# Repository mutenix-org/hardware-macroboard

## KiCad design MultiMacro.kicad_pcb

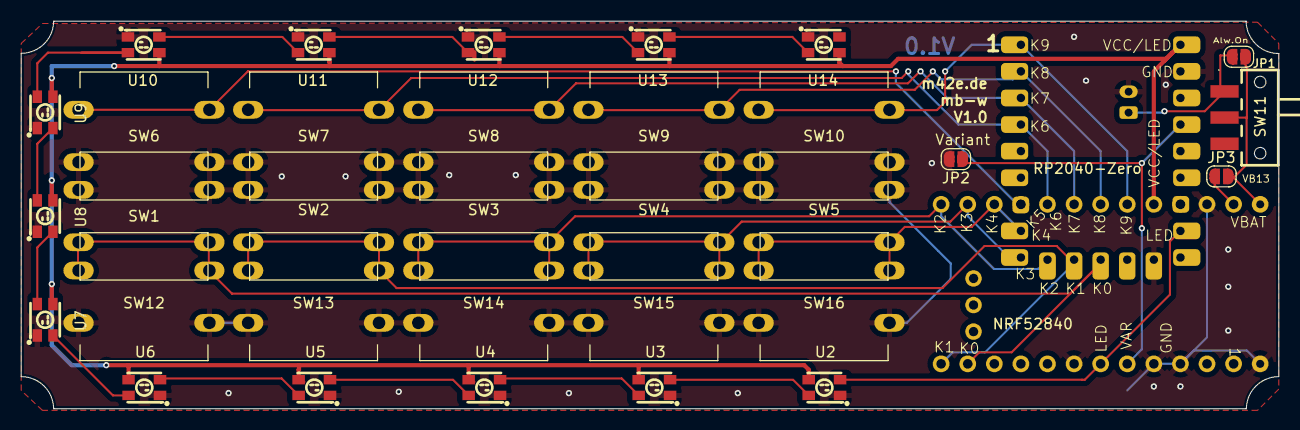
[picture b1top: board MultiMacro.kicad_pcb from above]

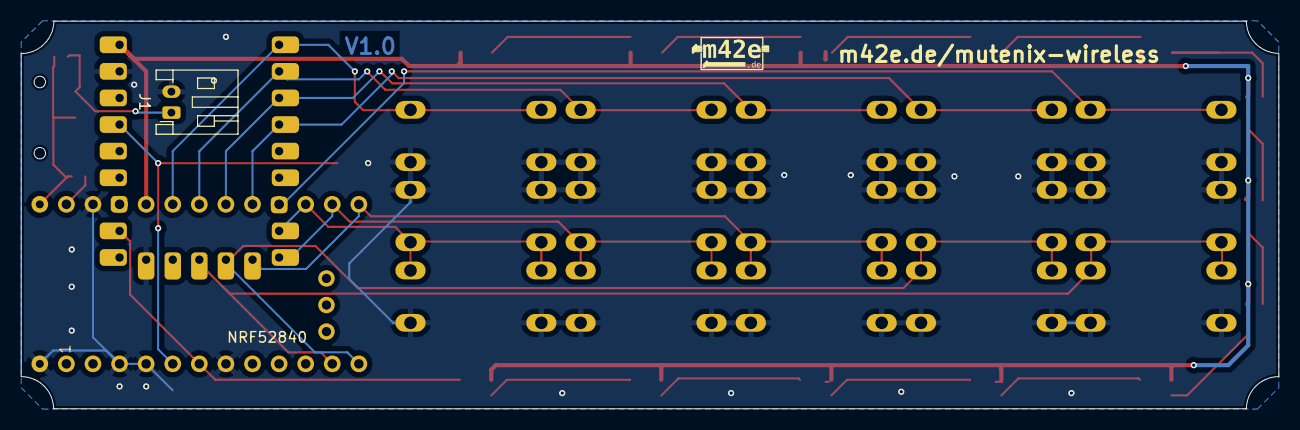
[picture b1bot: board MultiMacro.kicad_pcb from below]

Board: 2 copper layers, 120.1 x 37.0 mm, 35 parts (3 on the bottom side), 30 nets.

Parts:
J1: Conn_01x02; JST_PH_S2B-PH-K_1x02_P2.00mm_Horizontal
JP1, JP2, JP3: SolderJumper_2_Open; SolderJumper-2_P1.3mm_Open_RoundedPad1.0x1.5mm
RZ1: RP2040-Zero; RP2040-Zero2
SW1, SW2, SW3, SW4, SW5, SW6, SW7, SW8, SW9, SW10, SW12, SW13, SW14, SW15, SW16: SW_Push; SW_SPST_Omron_B3F-50xx
SW11: SW_SPDT_312; SW-SMD_K3-1280S-K1
U1: SuperMini nRF52840; SuperMini NRF52840
U2, U3, U4, U5, U6, U7, U8, U9, U10, U11, U12, U13, U14: XL-3528RGBC-WS2812B; LED-SMD_4P-L3.5-W2.8-BR-1

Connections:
/Keys0: RZ1.12 (GP11), SW1.1, SW12.1, U1.11 (P1.04-LF)
/Keys1: RZ1.11 (GP10), SW2.1, SW13.1, U1.12 (P1.06-LF)
/Keys2: RZ1.10 (GP9), SW3.1, SW14.1, U1.24 (P0.09-LF)
/Keys3: RZ1.9 (GP8), SW4.1, SW15.1, U1.23 (P0.10-LF)
/Keys4: RZ1.8 (GP7), SW5.1, SW16.1, U1.22 (P1.11-LF)
/Keys5: RZ1.7 (GP6), SW6.1, U1.21 (P1.13-LF)
/Keys6: RZ1.4 (GP3), SW7.1, U1.20 (P1.15-LF)
/Keys7: RZ1.3 (GP2), SW8.1, U1.19 (P0.02-LF)
/Keys8: RZ1.2 (GP1), SW9.1, U1.18 (P0.29-LF)
/Keys9: RZ1.1 (GP0), SW10.1, U1.17 (P0.31-LF)
GND: J1.2, JP2.2 (B), RZ1.14 (GP13), RZ1.23 (GND), SW1.2, SW2.2, SW3.2, SW4.2, SW5.2, SW6.2, SW7.2, SW8.2, SW9.2, SW10.2, SW12.2, SW13.2, SW14.2, SW15.2, SW16.2, U1.3 (GND), U1.4 (GND), U1.7 (P0.22), U1.14 (GND), U1.28 (GND), U2.1 (GND), U3.1 (GND), U4.1 (GND), U5.1 (GND), U6.1 (GND), U7.1 (GND), U8.1 (GND), U9.1 (GND), U10.1 (GND), U11.1 (GND), U12.1 (GND), U13.1 (GND), U14.1 (GND)
LED: RZ1.16 (GP15), U1.6 (P0.20), U2.2 (DI)
unnamed: J1.1, JP1.2 (B), SW11.1
unnamed: JP3.1 (A), U1.13 (BAT+)
unnamed: RZ1.17 (GP26), U1.15 (RST)
unnamed: U2.4 (DO), U3.2 (DI)
unnamed: U3.4 (DO), U4.2 (DI)
unnamed: U4.4 (DO), U5.2 (DI)
unnamed: U5.4 (DO), U6.2 (DI)
unnamed: U6.4 (DO), U7.2 (DI)
unnamed: U7.4 (DO), U8.2 (DI)
unnamed: U8.4 (DO), U9.2 (DI)
unnamed: U9.4 (DO), U10.2 (DI)
unnamed: U10.4 (DO), U11.2 (DI)
unnamed: U11.4 (DO), U12.2 (DI)
unnamed: U12.4 (DO), U13.2 (DI)
unnamed: U13.4 (DO), U14.2 (DI)
VARIANT: JP2.1 (A), RZ1.20 (GP29), U1.5 (P0.17)
VBAT: JP1.1 (A), JP3.2 (B), SW11.2, U1.29 (BAT+)
Vcc_LED: RZ1.22 (5V), U1.16 (3V3), U2.3 (VDD), U3.3 (VDD), U4.3 (VDD), U5.3 (VDD), U6.3 (VDD), U7.3 (VDD), U8.3 (VDD), U9.3 (VDD), U10.3 (VDD), U11.3 (VDD), U12.3 (VDD), U13.3 (VDD), U14.3 (VDD)

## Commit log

2025-01-14 feat: V1.0 of MacroBoard
2025-01-15 chore: add license
2025-01-26 chore: add license to source files and add pdf
2025-01-27 chore: Update license info in schematics

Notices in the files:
parts and their libraries:
Copyright: 2025 Matthias Bilger
SPDX-License-Identifier: CERN-OHL-S-2.0 license
